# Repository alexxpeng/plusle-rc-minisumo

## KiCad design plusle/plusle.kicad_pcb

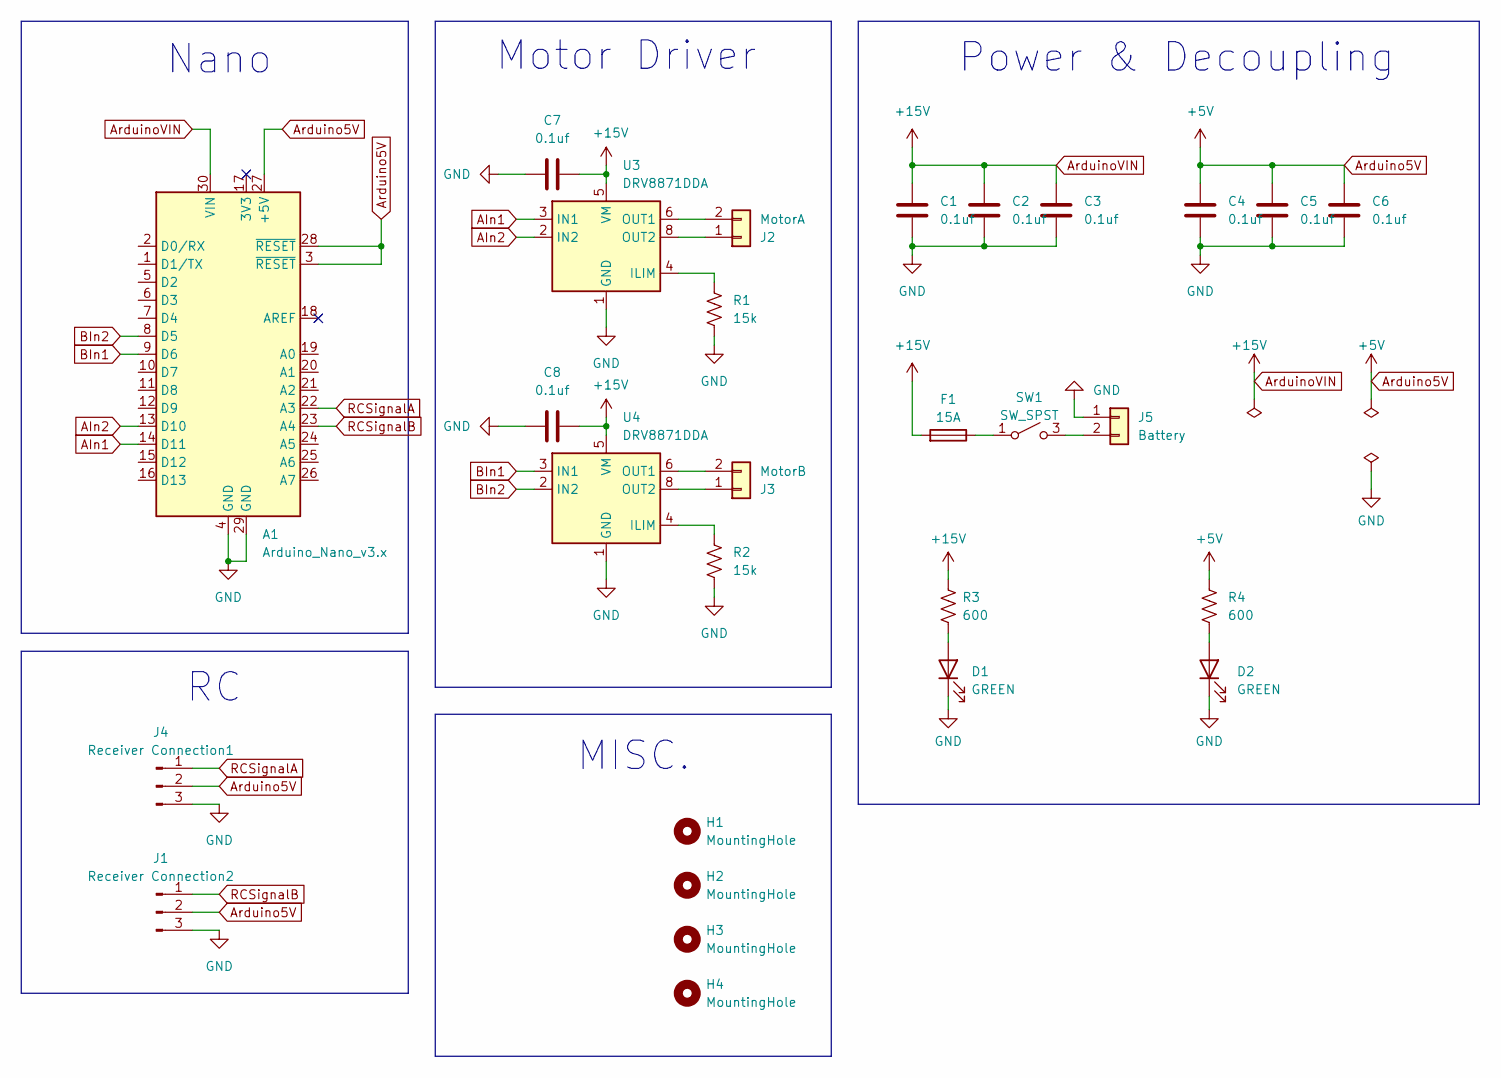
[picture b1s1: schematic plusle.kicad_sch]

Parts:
A1: Arduino_Nano_v3.x; Arduino_Nano
C1, C2, C3, C4, C5, C6, C7, C8: 0.1uf; C_0805_2012Metric_Pad1.18x1.45mm_HandSolder
D1, D2: GREEN; C_0603_1608Metric_Pad1.08x0.95mm_HandSolder
F1: 15A; Fuse_1206_3216Metric_Pad1.42x1.75mm_HandSolder
H1, H2, H3, H4: MountingHole; MountingHole_2.2mm_M2_ISO7380
J1: Receiver Connection2; PinHeader_1x03_P2.54mm_Vertical
J2: MotorA; TerminalBlock_Xinya_XY308-2.54-2P_1x02_P2.54mm_Horizontal
J3: MotorB; TerminalBlock_Xinya_XY308-2.54-2P_1x02_P2.54mm_Horizontal
J4: Receiver Connection1; PinHeader_1x03_P2.54mm_Vertical
J5: Battery; AMASS_XT30PW-M_1x02_P2.50mm_Horizontal
R1, R2: 15k; R_0805_2012Metric_Pad1.20x1.40mm_HandSolder
R3, R4: 600; D_0805_2012Metric_Pad1.15x1.40mm_HandSolder
SW1: SW_SPST; SW_AS11CP
U3, U4: DRV8871DDA; Texas_HTSOP-8-1EP_3.9x4.9mm_P1.27mm_EP2.95x4.9mm_Mask2.4x3.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

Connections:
AIn1: A1.14 (D11), U3.3 (IN1)
AIn2: A1.13 (D10), U3.2 (IN2)
Arduino5V: A1.3 (~RESET), A1.27 (+5V), A1.28 (~RESET), C4.1, C5.1, C6.1, J1.2, J4.2, R4.1
ArduinoVIN: A1.30 (VIN), C1.1, C2.1, C3.1, C7.2, C8.2, F1.2, R3.1, U3.5 (VM), U4.5 (VM)
BIn1: A1.9 (D6), U4.3 (IN1)
BIn2: A1.8 (D5), U4.2 (IN2)
GND: A1.4 (GND), A1.29 (GND), C1.2, C2.2, C3.2, C4.2, C5.2, C6.2, C7.1, C8.1, D1.1 (K), D2.1 (K), J1.3, J4.3, J5.1, R1.2, R2.2, U3.1 (GND), U3.7 (GND), U3.9 (GND), U4.1 (GND), U4.7 (GND), U4.9 (GND)
unnamed: D1.2 (A), R3.2
unnamed: D2.2 (A), R4.2
unnamed: J2.1, U3.8 (OUT2)
unnamed: J2.2, U3.6 (OUT1)
unnamed: J3.1, U4.8 (OUT2)
unnamed: J3.2, U4.6 (OUT1)
unnamed: J5.2, SW1.3 (B)
unnamed: F1.1, SW1.1 (A)
unnamed: R1.1, U3.4 (ILIM)
unnamed: R2.1, U4.4 (ILIM)
RCSignalA: A1.22 (A3), J4.1
RCSignalB: A1.23 (A4), J1.1

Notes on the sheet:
Power & Decoupling
Motor Driver
MISC.
Nano

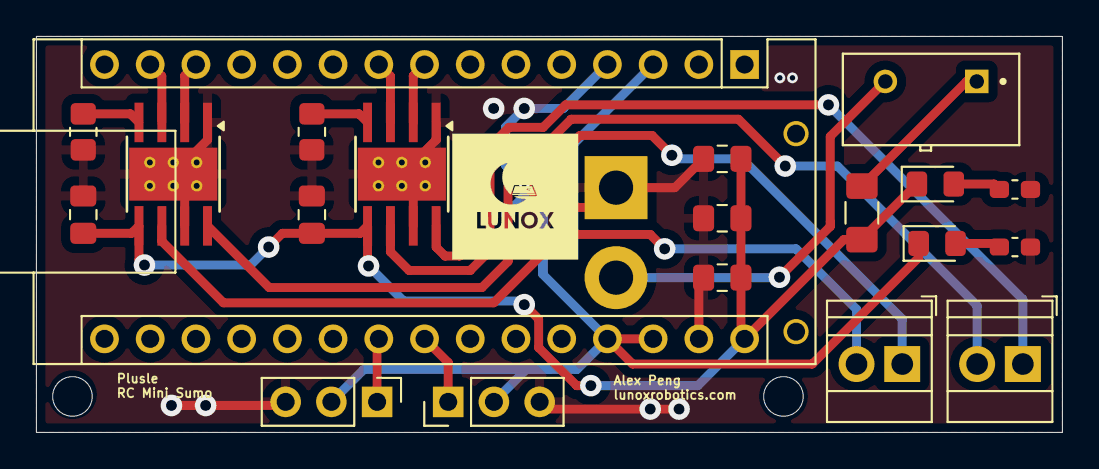
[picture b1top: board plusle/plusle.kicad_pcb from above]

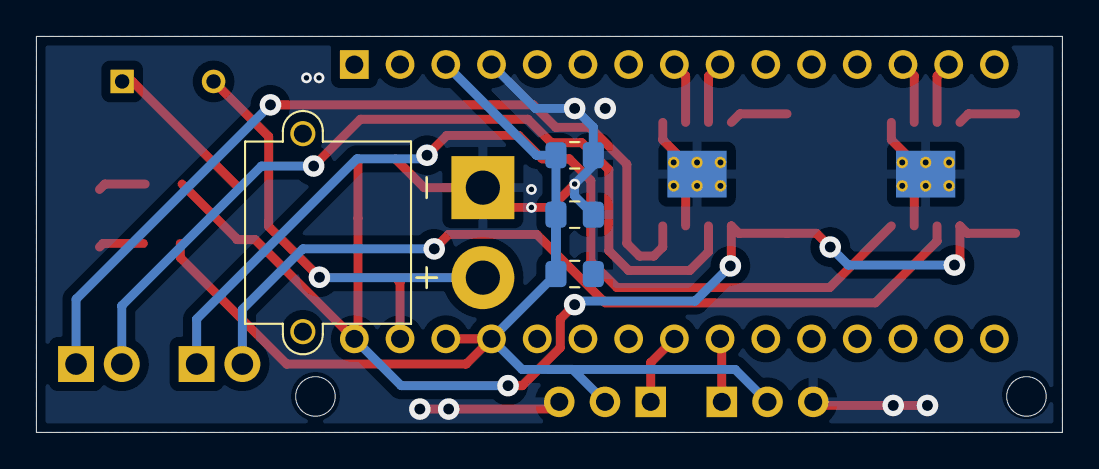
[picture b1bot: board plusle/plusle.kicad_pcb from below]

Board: 2 copper layers, 57.0 x 22.0 mm, 26 parts (4 on the bottom side), 19 nets.

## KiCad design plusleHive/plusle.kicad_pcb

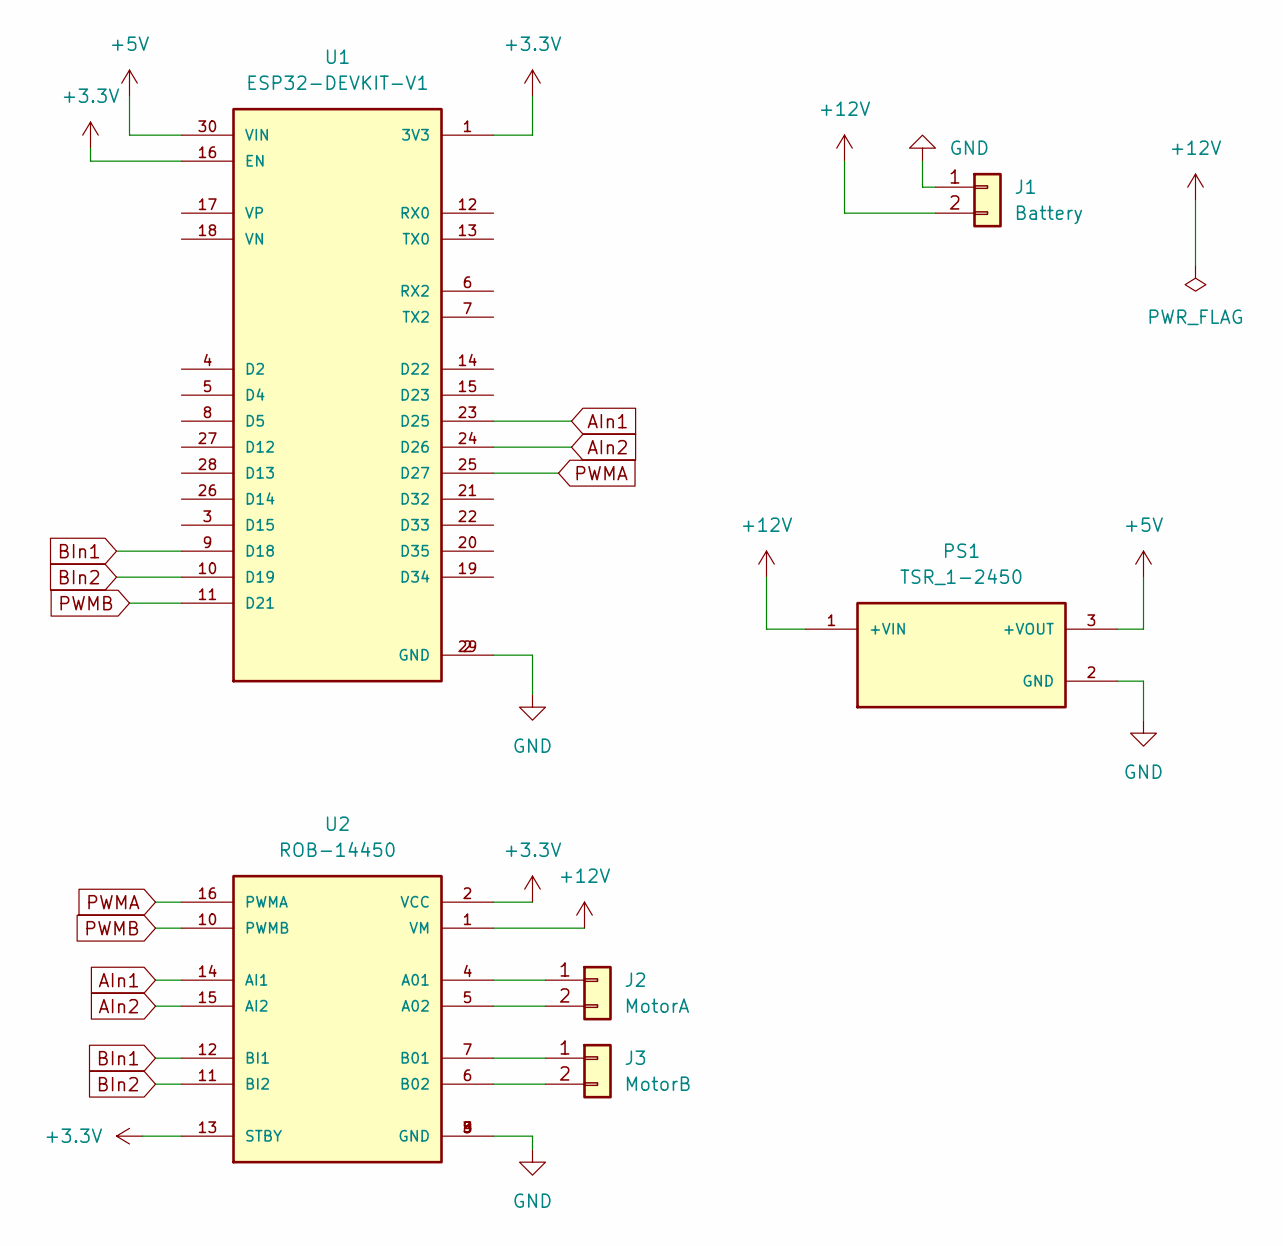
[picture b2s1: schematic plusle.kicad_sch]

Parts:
J1: Battery; TerminalBlock_Xinya_XY308-2.54-2P_1x02_P2.54mm_Horizontal
J2: MotorA; TerminalBlock_Xinya_XY308-2.54-2P_1x02_P2.54mm_Horizontal
J3: MotorB; TerminalBlock_Xinya_XY308-2.54-2P_1x02_P2.54mm_Horizontal
PS1: TSR_1-2450; CONV_TSR_1-2433; PARTREV Apr 27, 2020
U1: ESP32-DEVKIT-V1; MODULE_ESP32_DEVKIT_V1; PARTREV N/A
U2: ROB-14450; MODULE_ROB-14450; PARTREV 11-13-17

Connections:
+3.3V: U1.1 (3V3), U1.16 (EN), U2.2 (VCC), U2.13 (STBY)
+5V: PS1.3 (+VOUT), U1.30 (VIN)
+12V: J1.2, PS1.1 (+VIN), U2.1 (VM)
AIn1: U1.23 (D25), U2.14 (AI1)
AIn2: U1.24 (D26), U2.15 (AI2)
BIn1: U1.9 (D18), U2.12 (BI1)
BIn2: U1.10 (D19), U2.11 (BI2)
GND: J1.1, PS1.2 (GND), U1.2 (GND), U1.29 (GND), U2.3 (GND), U2.8 (GND), U2.9 (GND)
unnamed: J2.1, U2.4 (A01)
unnamed: J2.2, U2.5 (A02)
unnamed: J3.1, U2.7 (B01)
unnamed: J3.2, U2.6 (B02)
PWMA: U1.25 (D27), U2.16 (PWMA)
PWMB: U1.11 (D21), U2.10 (PWMB)

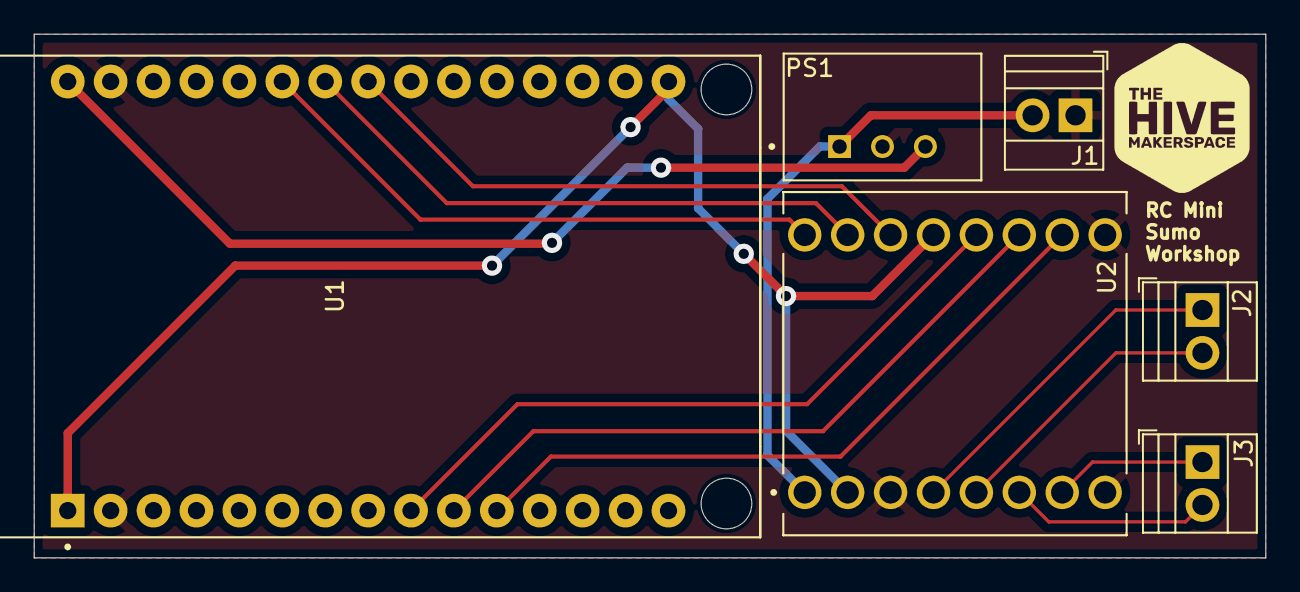
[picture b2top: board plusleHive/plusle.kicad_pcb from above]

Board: 2 copper layers, 72.9 x 31.0 mm, 6 parts (0 on the bottom side), 14 nets.

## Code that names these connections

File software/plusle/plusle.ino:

#define AIN1 11
#define AIN2 10
#define BIN1 6
#define BIN2 5
#define CH_A A3 // Channel A (forward/backward speed)
#define CH_B A4 // Channel B (left/right steering and speed)

void setup() {
  pinMode(AIN1, OUTPUT);
  pinMode(AIN2, OUTPUT);
  pinMode(BIN1, OUTPUT);
  pinMode(BIN2, OUTPUT);
  pinMode(CH_A, INPUT);
  pinMode(CH_B, INPUT);
}

void loop() {
  int pwmA = pulseIn(CH_A, HIGH);
  int pwmB = pulseIn(CH_B, HIGH);

  int baseSpeed = 0; // Base forward/backward speed
  int steerAdjustment = 0; // Adjustment for turning
  int speedA = 0;
  int speedB = 0;

  // Motor control for forward/backward movement
  if (pwmA > 1600) { // Threshold for forward
    baseSpeed = -map(pwmA, 1600, 2020, 0, 255); // Adjust speed
  } else if (pwmA < 1400) { // Threshold for backward
    baseSpeed = map(pwmA, 980, 1400, 255, 0); // Adjust speed
  }

  // Motor control for left/right steering
  if (pwmB > 1600) { // Threshold for right
    steerAdjustment = map(pwmB, 1600, 2020, 0, 255); // Adjust speed
  } else if (pwmB < 1400) { // Threshold for left
    steerAdjustment = -map(pwmB, 980, 1400, 255, 0); // Adjust speed
  }

  // Combine base speed with steering adjustment
  speedA = baseSpeed + steerAdjustment;
  speedB = baseSpeed - steerAdjustment;

  // Apply motor speeds
  if (speedA > 0) {
    analogWrite(AIN1, speedA);
    analogWrite(AIN2, 0);
  } else if (speedA < 0) {
    analogWrite(AIN1, 0);
    analogWrite(AIN2, -speedA);
  } else {
    analogWrite(AIN1, 255);
    analogWrite(AIN2, 255);
  }

  if (speedB > 0) {
    analogWrite(BIN1, speedB);
    analogWrite(BIN2, 0);
  } else if (speedB < 0) {
    analogWrite(BIN1, 0);
    analogWrite(BIN2, -speedB);
  } else {
    analogWrite(BIN1, 255);
    analogWrite(BIN2, 255);
  }

  delay(5); // Small delay for stability
}

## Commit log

2025-01-30 complete
    rough draft complete
2025-02-01 created board and schematic
    completed basic board and schematic for hive workshop
2025-02-08 added working software
    working for elegoo esp32 wroom and bluefruit connect app
2025-02-09 updated
    updated layout and schematic for hive bot (powered by 9v battery with switch)
2025-03-04 NewIteration
    new compact board for personal plusle project, non-hive
2025-03-24 updated plusle code
    Proper remote control input mapping
